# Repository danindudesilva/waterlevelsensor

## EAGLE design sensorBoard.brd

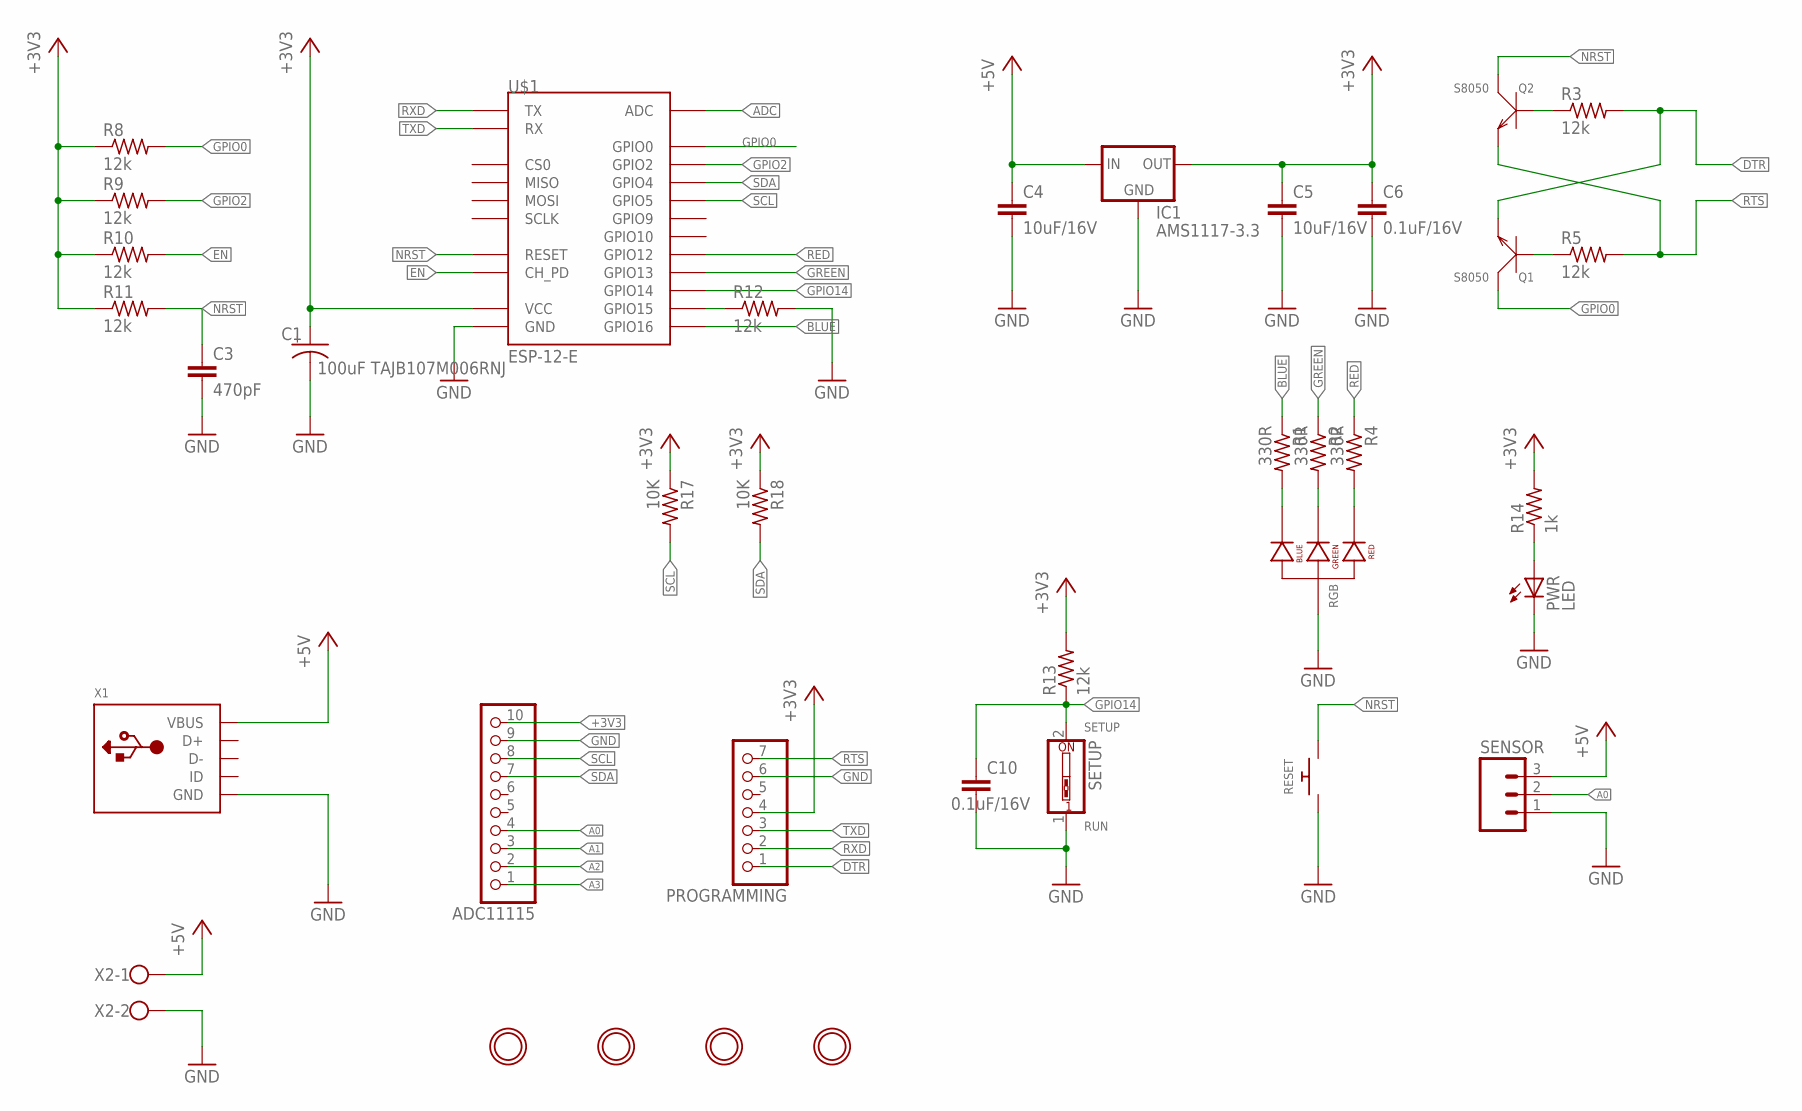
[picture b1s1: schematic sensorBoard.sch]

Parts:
ADC11115: PINHD-1X10; 1X10
C1: 100uF TAJB107M006RNJ; A/3216-18R
C3: 470pF; C0805K
C4, C5: 10uF/16V; C0805K
C6, C10: 0.1uF/16V; C0805K
IC1: AMS1117-3.3; SOT223
PROGRAMMING: PINHD-1X7; 1X07
PWR: LED; CHIP-LED0805
Q1, Q2: S8050; SOT-23
R1, R2, R4: 330R; M0805
R3, R5, R8, R9, R10, R11, R12, R13: 12k; M0805
R14: 1k; M0805
R17, R18: 10K; M0805
RESET: SWITCH_PUSHBUTTONEVQ-PE; TACT_PANA-EVQ
RGB: LED-RGB-CA-THRUCLEAR; LED-RGB-THRU
SENSOR: M03JST-PTH-VERT; JST-3-PTH-VERT
SETUP: SW_DIP-1; EDG-01
U$1: ESP-12-E
U$3, U$4, U$5, U$6: MOUNTINGHOLE2.5; MOUNTINGHOLE_2.5_PLATED
X1: USB_MICRO_20329_V2; 4UCONN_20329_V2
X2: W237-102

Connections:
+3V3: ADC11115.10, C1.+, C5.1, C6.1, IC1.2 (OUT), PROGRAMMING.4, R8.1, R9.1, R10.1, R11.1, R13.2, R14.2, R17.1, R18.1, U$1.VCC
+5V: C4.1, IC1.3 (IN), SENSOR.3, X1.VBUS, X2.1
A0: ADC11115.4, SENSOR.2
A1: ADC11115.3
A2: ADC11115.2
A3: ADC11115.1
ADC: U$1.ADC
BLUE: R1.1, U$1.GPIO16
DTR: PROGRAMMING.1, Q1.2 (E), R3.2
EN: R10.2, U$1.CH_PD
GND: ADC11115.9, C1.-, C3.2, C4.2, C5.2, C6.2, C10.2, IC1.1 (GND), PROGRAMMING.6, PWR.C, R12.2, RESET.P$1, RGB.2 (ANODE), SENSOR.1, SETUP.1, U$1.GND, X1.BASE@1 (GND), X1.BASE@2 (GND), X1.GND, X1.SPRT@1 (GND), X1.SPRT@2 (GND), X1.SPRT@3 (GND), X1.SPRT@4 (GND), X2.2
GPIO0: Q1.3 (C), R8.2, U$1.GPIO0
GPIO2: R9.2, U$1.GPIO2
GPIO14: C10.1, R13.1, SETUP.2, U$1.GPIO14
GREEN: R2.1, U$1.GPIO13
unnamed: Q2.1 (B), R3.1
unnamed: Q1.1 (B), R5.1
unnamed: R12.1, U$1.GPIO15
unnamed: PWR.A, R14.1
unnamed: R4.2, RGB.1 (RED_CATHODE)
unnamed: R2.2, RGB.3 (GREEN_CATHODE)
unnamed: R1.2, RGB.4 (BLUE_CATHODE)
NRST: C3.1, Q2.3 (C), R11.2, RESET.P$2, U$1.RESET
RED: R4.1, U$1.GPIO12
RTS: PROGRAMMING.7, Q2.2 (E), R5.2
RXD: PROGRAMMING.2, U$1.TX
SCL: ADC11115.8, R17.2, U$1.GPIO5
SDA: ADC11115.7, R18.2, U$1.GPIO4
TXD: PROGRAMMING.3, U$1.RX

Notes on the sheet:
RUN
SETUP

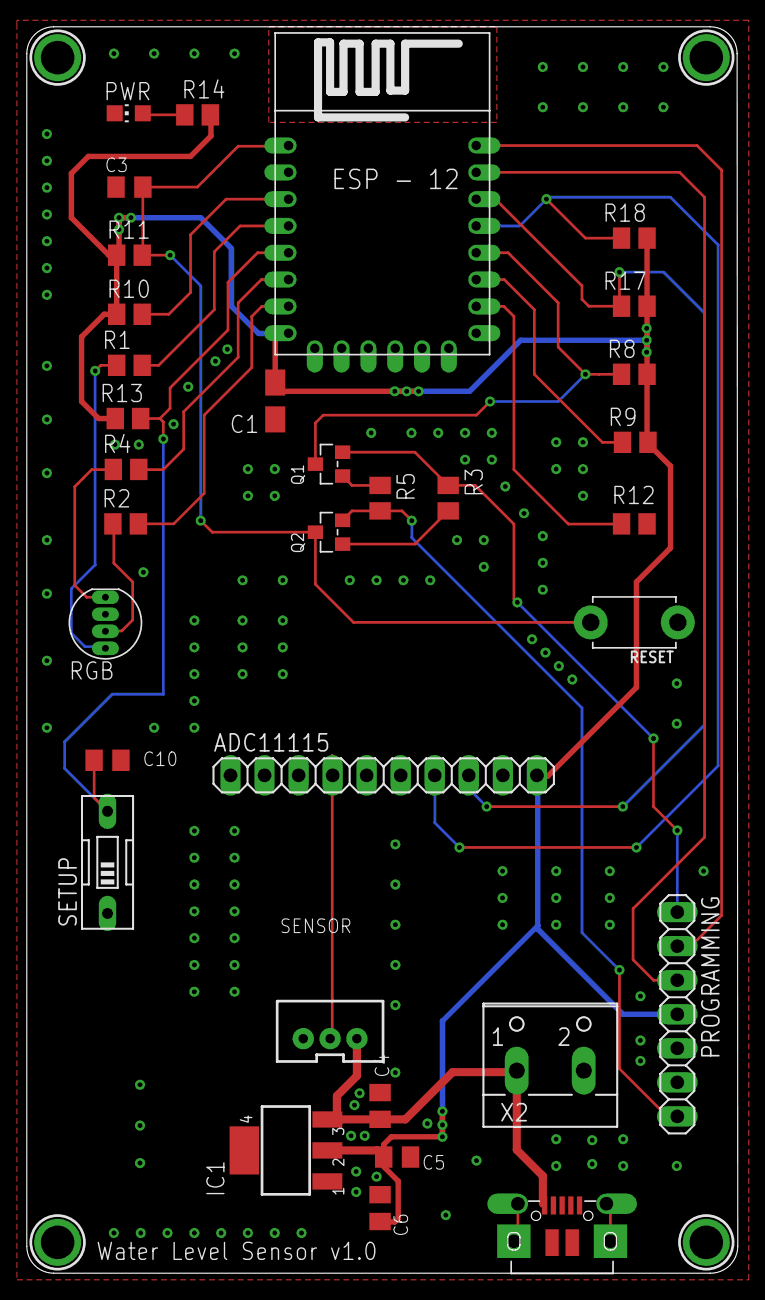
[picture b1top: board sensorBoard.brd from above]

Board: 2 copper layers, 53.0 x 93.0 mm, 37 parts (0 on the bottom side), 25 nets.

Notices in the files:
parts and their libraries:
SparkFun-Connectors: Licensing: Creative Commons ShareAlike 4.0 International - https://creativecommons.org/licenses/by-sa/4.0
